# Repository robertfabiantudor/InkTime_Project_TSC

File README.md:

# InkTime Smartwatch

<br/>
<br/>

## Block Diagram

<br/>
<br/>

## Bill of Materials(BOM)

| Name | Component Type | Part Number | Qty | JLCPCB Part Link | Datasheet Link|
|----------|----------|------------|-----|----------------|-----------|
| ANT1 | Antenna | 2450AT18B100E | 1 | [View Part](https://jlcpcb.com/partdetail/JohansonDielectrics-2450AT18B100E/C2917717) | [View Datasheet](https://www.lcsc.com/datasheet/C2917717.pdf?spm=wm.sxq.inf.ggs___wm.ssy.bg.0.xh&lcsc_vid=RVILV1QAFgMLXlRXRFQPBVVeFgVaXwJQTwdfAlJXFAUxVlNRQVReVFZST1FWUDsOAxUeFF5JWBYZEEoKFBINSQcJGk4%3D) |
| C1, C2, C17, C18 | Capacitor | GRM0335C1H120JA01D | 4 | [View Part](https://jlcpcb.com/partdetail/MurataElectronics-GRM0335C1H120JA01D/C85890) | [View Datasheet](https://www.lcsc.com/datasheet/C85890.pdf?spm=wm.sxq.inf.ggs___wm.ssy.bg.0.xh&lcsc_vid=RVILV1QAFgMLXlRXRFQPBVVeFgVaXwJQTwdfAlJXFAUxVlNRQVReVFZQQFRdUzsOAxUeFF5JWBYZEEoKFBINSQcJGk4eFQsCAgIaSgADAwAHC0slRVhfUFNXQE8GEwkK) |
| C1-EP-DR, C24, C39 | Capacitor | GRM155R60J106ME44D | 3 | [View Part](https://jlcpcb.com/partdetail/MurataElectronics-GRM155R60J106ME44D/C76991) | [View Datasheet](https://www.lcsc.com/datasheet/C76991.pdf?spm=wm.sxq.inf.ggs___wm.ssy.bg.0.xh&lcsc_vid=RVILV1QAFgMLXlRXRFQPBVVeFgVaXwJQTwdfAlJXFAUxVlNRQVReVFdWQ1NfVTsOAxUeFF5JWBYZEEoKFBINSQcJGk4eFQsCAgIaSgADAwAHC0slT1RWXlRIHxUDCw%3D%3D) |
| C2-EP-DR | Capacitor | RVT1E4R7M0405 | 1 | [View Part](https://jlcpcb.com/partdetail/DMBJ-RVT1E4R7M0405_4_7UF25V/C970600) | [View Datasheet](https://www.lcsc.com/datasheet/C2895731.pdf?spm=wm.sxq.inf.ggs___wm.ssy.bg.0.xh&lcsc_vid=RVILV1QAFgMLXlRXRFQPBVVeFgVaXwJQTwdfAlJXFAUxVlNRQVReVFdRRVlcUjsOAxUeFF5JWBYZEEoKFBINSQcJGk4eFQsCAgIaSgADAwAHC0slRVlXUlNVRk8GEwkK) |
| C3, C4 | Capacitor | GRM0335C1H1R0BA01D | 2 | [View Part](https://jlcpcb.com/partdetail/MurataElectronics-GRM0335C1H1R0BA01D/C85893) | [View Datasheet](https://www.lcsc.com/datasheet/C85893.pdf?spm=wm.sxq.inf.ggs___wm.ssy.bg.0.xh&lcsc_vid=RVILV1QAFgMLXlRXRFQPBVVeFgVaXwJQTwdfAlJXFAUxVlNRQVReVFFVTlldVzsOAxUeFF5JWBYZEEoKFBINSQcJGk4dAgUUFAk%3D) |
| C5, C7, C8, C12, C19 | Capacitor | GRM033R60J104KE19D | 5 | [View Part](https://jlcpcb.com/partdetail/MurataElectronics-GRM033R60J104KE19D/C76928) | [View Datasheet](https://www.lcsc.com/datasheet/C76928.pdf?spm=wm.sxq.inf.ggs___wm.ssy.bg.0.xh&lcsc_vid=RVILV1QAFgMLXlRXRFQPBVVeFgVaXwJQTwdfAlJXFAUxVlNRQVReVFJTQlJcVDsOAxUeFF5JWBYZEEoKFBINSQcJGk4eFQsCAgIaSgADAwAHC0slRVlXUlNVRk8GEwkK) |
| C6, C14, C20, C21, C43 | Capacitor | GRM155R60J475KE96D | 5 | [View Part](https://jlcpcb.com/partdetail/MurataElectronics-GRM155R60J475KE96D/C76995) | [View Datasheet](https://www.lcsc.com/datasheet/C76995.pdf?spm=wm.sxq.inf.ggs___wm.ssy.bg.0.xh&lcsc_vid=RVILV1QAFgMLXlRXRFQPBVVeFgVaXwJQTwdfAlJXFAUxVlNRQVReVFNRR1VbVjsOAxUeFF5JWBYZEEoKFBINSQcJGk4dAgUUFAk%3D) |
| C9 | Capacitor | GRM033R71E821KA01D | 1 | [View Part](https://jlcpcb.com/partdetail/197002-GRM033R71E821KA01D/C185597) | [View Datasheet](https://www.lcsc.com/datasheet/C185597.pdf?spm=wm.sxq.inf.ggs___wm.ssy.bg.0.xh&lcsc_vid=RVILV1QAFgMLXlRXRFQPBVVeFgVaXwJQTwdfAlJXFAUxVlNRQVReVFxTQVVfVjsOAxUeFF5JWBYZEEoKFBINSQcJGk4dAgUUFAk%3D) |
| C11 | Capacitor | GRM0335C1E101JA01D | 1 | [View Part](https://jlcpcb.com/partdetail/MurataElectronics-GRM0335C1E101JA01D/C76917) | [View Datasheet](https://www.lcsc.com/datasheet/C76917.pdf?spm=wm.sxq.inf.ggs___wm.ssy.bg.0.xh&lcsc_vid=RVILV1QAFgMLXlRXRFQPBVVeFgVaXwJQTwdfAlJXFAUxVlNRQVReVF1QQ1JXVzsOAxUeFF5JWBYZEEoKFBINSQcJGk4eFQsCAgIaSgADAwAHC0slRlRfX1ZWT08GEwkK) |
| C15 | Capacitor | GRM155R60J105KE19D | 1 | [View Part](https://jlcpcb.com/partdetail/MurataElectronics-GRM155R60J105KE19D/C15684) | [View Datasheet](https://www.lcsc.com/product-detail/C15684.html?s_z=n_q_GRM155R60J105KE19D&spm=wm.ssy.bg.0.xh&lcsc_vid=RVILV1QAFgMLXlRXRFQPBVVeFgVaXwJQTwdfAlJXFAUxVlNRQVReU1ZQR1NbVTsOAxUeFF5JWBYZEEoKFBINSQcJGk4dAgUUFAk%3D) |
| C16, C10, C13, C22 | Capacitor | GRM033R60J473KE19D | 4 | [View Part](https://jlcpcb.com/parts/componentSearch?searchTxt=GRM033R60J473KE19D) | [View Datasheet](https://www.lcsc.com/product-detail/C85925.html?s_z=n_q_GRM033R60J473KE19D&spm=wm.ssy.bg.0.xh&lcsc_vid=RVILV1QAFgMLXlRXRFQPBVVeFgVaXwJQTwdfAlJXFAUxVlNRQVReU1RRTlFcUzsOAxUeFF5JWBYZEEoKFBINSQcJGk4dAgUUFAk%3D) |
| C25, C33 | Capacitor | GRM155R60J226ME11D | 2 | [View Part](https://jlcpcb.com/partdetail/408393-GRM155R60J226ME11D/C415703) | [View Datasheet](https://www.lcsc.com/datasheet/C415703.pdf?spm=wm.sxq.inf.ggs___wm.ssy.bg.0.xh&lcsc_vid=RVILV1QAFgMLXlRXRFQPBVVeFgVaXwJQTwdfAlJXFAUxVlNRQVReU1BSQlVdVjsOAxUeFF5JWBYZEEoKFBINSQcJGk4dAgUUFAk%3D) |
| C23, C27, C29, C30, C31, C32, C34, C37, C38, C42| Capacitor | GRM011R60J152KE01L | 10 | [View Part](https://jlcpcb.com/partdetail/22429554-GRM011R60J152KE01L/C21012218) | [View Datasheet](https://www.lcsc.com/datasheet/C21012218.pdf?spm=wm.sxq.inf.ggs___wm.ssy.bg.0.xh&lcsc_vid=RVILV1QAFgMLXlRXRFQPBVVeFgVaXwJQTwdfAlJXFAUxVlNRQVReU1FTRlhfUDsOAxUeFF5JWBYZEEoKFBINSQcJGk4eFQsCAgIaSgADAwAHC0slQFdXXlFIHxUDCw%3D%3D) |
| D2, D4, D5  | Schottky Diode | MBR0530 | 3 | [View Part](https://jlcpcb.com/partdetail/onsemi-MBR0530/C232832) | [View Datasheet](https://www.lcsc.com/datasheet/C232832.pdf?spm=wm.sxq.inf.ggs___wm.ssy.bg.3.xh&lcsc_vid=RVILV1QAFgMLXlRXRFQPBVVeFgVaXwJQTwdfAlJXFAUxVlNRQVReUlVUQlZXXjsOAxUeFF5JWBYZEEoKFBINSQcJGk4eFQsCAgIaSgADAwAHC0slQ1ZbUFVeWQkaCgg%3D) |
| D3 | ESD Protection | USBLC6-2SC6Y | 1 | [View Part](https://jlcpcb.com/partdetail/STMicroelectronics-USBLC62SC6Y/C2969755) | [View Datasheet](https://www.lcsc.com/datasheet/C2969755.pdf?spm=wm.sxq.inf.ggs___wm.ssy.bg.0.xh&lcsc_vid=RVILV1QAFgMLXlRXRFQPBVVeFgVaXwJQTwdfAlJXFAUxVlNRQVReUlZVQFReVjsOAxUeFF5JWBYZEEoKFBINSQcJGk4dAgUUFAk%3D) |
| EPD_C1, EPD_C2, EPD_C6–EPD_C12 | Capacitor | 0201WMJ0100TCE | 9 | [View Part](https://jlcpcb.com/partdetail/25795-0201WMJ0100TCE/C25052) | [View Datasheet](https://www.lcsc.com/datasheet/C25052.pdf?spm=wm.sxq.inf.ggs___wm.ssy.bg.0.xh&lcsc_vid=RVILV1QAFgMLXlRXRFQPBVVeFgVaXwJQTwdfAlJXFAUxVlNRQVReUVVSQFBcUjsOAxUeFF5JWBYZEEoKFBINSQcJGk4eFQsCAgIaSgADAwAHC0slRlNcU1dSWQkaCgg%3D) |
| EPD_C5 | Capacitor | 500R07W104KV4T | 1 | [View Part](https://jlcpcb.com/partdetail/6103901-500R07W104KV4T_0_1uF50v/C5337557) | [View Datasheet](https://www.mouser.com/catalog/specsheets/johanson_joha-s-a0008490164-1.pdf?_gl=1*1natqy3*_gcl_aw*R0NMLjE3NzY0NTE3MzMuQ2p3S0NBand0SWZQQmhBekVpd0F2OVJUSnBRX2lCajR0MlBzNHZ5MExvUnpFdC1mTmpicTQwR0hYM3ZmV1lEa1JYZ2ZDUGdWczVxMHBob0MyMXdRQXZEX0J3RQ..*_gcl_au*MTQ2MTI4OTM2Mi4xNzc2NDUxNjg3LjE4ODk2NzQyODAuMTc3NjUwMjIwNy4xNzc2NTAyNzAz*_ga*MTg0MjYwMjQxLjE3NzY0NTE2ODc.*_ga_15W4STQT4T*czE3NzY1MDYyOTckbzQkZzEkdDE3NzY1MDYzNjEkajYwJGwwJGgw) |
| IC1 | LiPo Charger | BQ25180YBGR | 1 | [View Part](https://jlcpcb.com/partdetail/TexasInstruments-BQ25180YBGR/C3682423) | [View Datasheet](https://www.ti.com/cn/lit/gpn/bq25180) |
| IC2 | Haptic Driver | DRV2605YZFR | 1 | [View Part](https://jlcpcb.com/partdetail/TexasInstruments-DRV2605YZFR/C81079) | [View Datasheet](https://www.lcsc.com/datasheet/C81079.pdf?spm=wm.sxq.inf.ggs___wm.ssy.bg.0.xh&lcsc_vid=RVILV1QAFgMLXlRXRFQPBVVeFgVaXwJQTwdfAlJXFAUxVlNRQVReUldeQ1RfVjsOAxUeFF5JWBYZEEoKFBINSQcJGk4eFQsCAgIaSgADAwAHC0slQ1BbUFRVWQkaCgg%3D) |
| IC3 | IMU | BMA421 | 1 | [View Part](https://jlcpcb.com/partdetail/BoschSensortec-BMA421/C5242966) | [View Datasheet](https://files.pine64.org/doc/datasheet/pinetime/BST-BMA421-FL000.pdf) |
| IC9 | DC/DC Converter | RT6160AWSC | 1 | [View Part](https://jlcpcb.com/partdetail/RichtekTech-RT6160AWSC/C7065276) | [View Datasheet](https://www.lcsc.com/datasheet/C7065276.pdf?spm=wm.sxq.inf.ggs___wm.ssy.bg.0.xh&lcsc_vid=RVILV1QAFgMLXlRXRFQPBVVeFgVaXwJQTwdfAlJXFAUxVlNRQVReUlFfQVZbUTsOAxUeFF5JWBYZEEoKFBINSQcJGk4dAgUUFAk%3D) |
| J1 | FPC Connector | 503480-2400 | 1 | [View Part](https://jlcpcb.com/partdetail/MOLEX-5034802400/C122434) | [View Datasheet](https://www.lcsc.com/datasheet/C122434.pdf?spm=wm.sxq.inf.ggs___wm.ssy.bg.0.xh&lcsc_vid=RVILV1QAFgMLXlRXRFQPBVVeFgVaXwJQTwdfAlJXFAUxVlNRQVReUlJeQ1JeVzsOAxUeFF5JWBYZEEoKFBINSQcJGk4dAgUUFAk%3D) |
| J2 | Debug Connector | TC2030-IDC | 1 | - | [View Datasheet](https://www.tag-connect.com/wp-content/uploads/bsk-pdf-manager/2019/12/TC2030-IDC-Datasheet-Rev-B.pdf) |
| J4 | USB-C Connector | KH-TYPE-C-16P | 1 | [View Part](https://jlcpcb.com/partdetail/Shenzhen_KinghelmElec-KH_TYPE_C16P/C709357) | [View Datasheet](https://www.lcsc.com/datasheet/C709357.pdf?spm=wm.sxq.inf.ggs___wm.ssy.bg.0.xh&lcsc_vid=RVILV1QAFgMLXlRXRFQPBVVeFgVaXwJQTwdfAlJXFAUxVlNRQVReUlNQQldXVDsOAxUeFF5JWBYZEEoKFBINSQcJGk4eFQsCAgIaSgADAwAHC0slRFdWVVBURE8GEwkK) |
| L1 | Inductor | LQG15HS3N9S02D | 1 | [View Part](https://jlcpcb.com/partdetail/MurataElectronics-LQG15HS3N9S02D/C77109) | [View Datasheet](https://www.lcsc.com/datasheet/C77109.pdf?spm=wm.sxq.inf.ggs___wm.ssy.bg.0.xh&lcsc_vid=RVILV1QAFgMLXlRXRFQPBVVeFgVaXwJQTwdfAlJXFAUxVlNRQVReUVBfQVJdVjsOAxUeFF5JWBYZEEoKFBINSQcJGk4dAgUUFAk%3D) |
| L2 | Inductor | LQW15DN100M00D | 1 | [View Part](https://jlcpcb.com/partdetail/MurataElectronics-LQW15DN100M00D/C910650) | [View Datasheet](https://www.lcsc.com/datasheet/C910650.pdf?spm=wm.sxq.inf.ggs___wm.ssy.bg.0.xh&lcsc_vid=RVILV1QAFgMLXlRXRFQPBVVeFgVaXwJQTwdfAlJXFAUxVlNRQVReUVJXR1BdVjsOAxUeFF5JWBYZEEoKFBINSQcJGk4eFQsCAgIaSgADAwAHC0slRVReUlZIHxUDCw%3D%3D) |
| L3 | Inductor | LQG15HS15NJ02D| 1 | [View Part](https://jlcpcb.com/partdetail/MurataElectronics-LQG15HS15NJ02D/C86059) | [View Datasheet](https://www.lcsc.com/datasheet/C86059.pdf?spm=wm.sxq.inf.ggs___wm.ssy.bg.0.xh&lcsc_vid=RVILV1QAFgMLXlRXRFQPBVVeFgVaXwJQTwdfAlJXFAUxVlNRQVReUVJfRlJaVzsOAxUeFF5JWBYZEEoKFBINSQcJGk4dAgUUFAk%3D) |
| L5 | Inductor | LQG15HS27NJ02D | 1 | [View Part](https://jlcpcb.com/partdetail/MurataElectronics-LQG15HS27NJ02D/C12669) | [View Datasheet](https://www.lcsc.com/datasheet/C12669.pdf?spm=wm.sxq.inf.ggs___wm.ssy.bg.0.xh&lcsc_vid=RVILV1QAFgMLXlRXRFQPBVVeFgVaXwJQTwdfAlJXFAUxVlNRQVReUVNVR1hcXzsOAxUeFF5JWBYZEEoKFBINSQcJGk4dAgUUFAk%3D) |
| L7 | Inductor | LQW15CNR47K10D| 1 | [View Part](https://jlcpcb.com/partdetail/MurataElectronics-LQW15CNR47K10D/C913544) | [View Datasheet](https://www.lcsc.com/datasheet/C913544.pdf?spm=wm.sxq.inf.ggs___wm.ssy.bg.0.xh&lcsc_vid=RVILV1QAFgMLXlRXRFQPBVVeFgVaXwJQTwdfAlJXFAUxVlNRQVReUVNRT1dbVjsOAxUeFF5JWBYZEEoKFBINSQcJGk4eFQsCAgIaSgADAwAHC0slQFZfV11IHxUDCw%3D%3D) |
| Q1 | P-Channel MOSFET | DMG2305UX-7 | 1 | [View Part](https://jlcpcb.com/partdetail/DiodesIncorporated-DMG2305UX7/C150470) | [View Datasheet](https://www.lcsc.com/datasheet/C150470.pdf?spm=wm.sxq.inf.ggs___wm.ssy.bg.0.xh&lcsc_vid=RVILV1QAFgMLXlRXRFQPBVVeFgVaXwJQTwdfAlJXFAUxVlNRQVReUVxRQFhXUzsOAxUeFF5JWBYZEEoKFBINSQcJGk4dAgUUFAk%3D) |
| Q3 | N-Channel MOSFET | SI1308EDL-T1-GE3 | 1 | [View Part](https://jlcpcb.com/partdetail/VishayIntertech-SI1308EDL_T1GE3/C469327) | [View Datasheet](https://www.lcsc.com/datasheet/C469327.pdf?spm=wm.sxq.inf.ggs___wm.ssy.bg.0.xh&lcsc_vid=RVILV1QAFgMLXlRXRFQPBVVeFgVaXwJQTwdfAlJXFAUxVlNRQVReUVBWQ1VdVDsOAxUeFF5JWBYZEEoKFBINSQcJGk4eFQsCAgIaSgADAwAHC0slQFFYUlZRQU8GEwkK) |
| R_PWR_EPD, R2_EP_DR, R9 | Resistor | CPF0201D10KC1 | 3 | [View Part](https://jlcpcb.com/partdetail/TEConnectivity-CPF0201D10KC1/C4187156) | [View Datasheet](https://www.lcsc.com/datasheet/C4187156.pdf?spm=wm.sxq.inf.ggs___wm.ssy.bg.0.xh&lcsc_vid=RVILV1QAFgMLXlRXRFQPBVVeFgVaXwJQTwdfAlJXFAUxVlNRQVReUFdQR1hYVjsOAxUeFF5JWBYZEEoKFBINSQcJGk4eFQsCAgIaSgADAwAHC0slRlReU1NWWQkaCgg%3D) |
| R_TYPE_SEL | Resistor | RC0201FR-072R2L | 1 | [View Part](https://jlcpcb.com/partdetail/YAGEO-RC0201FR072R2L/C138154) | [View Datasheet](https://www.lcsc.com/datasheet/C138154.pdf?spm=wm.sxq.inf.ggs___wm.ssy.bg.0.xh&lcsc_vid=RVILV1QAFgMLXlRXRFQPBVVeFgVaXwJQTwdfAlJXFAUxVlNRQVReUFBTQlhcVDsOAxUeFF5JWBYZEEoKFBINSQcJGk4dAgUUFAk%3D) |
| R1_EP_DR | Resistor | 25121WF470LT4E | 1 | [View Part](https://jlcpcb.com/partdetail/21809-25121WF470LT4E/C21097) | [View Datasheet](https://www.lcsc.com/datasheet/C21097.pdf?spm=wm.sxq.inf.ggs___wm.ssy.bg.0.xh&lcsc_vid=RVILV1QAFgMLXlRXRFQPBVVeFgVaXwJQTwdfAlJXFAUxVlNRQVReUFJWT1lbVTsOAxUeFF5JWBYZEEoKFBINSQcJGk4dAgUUFAk%3D) |
| R1_USB1, R2_USB | Resistor | RC0201JR-075K1L | 2 | [View Part](https://jlcpcb.com/partdetail/YAGEO-RC0201JR075K1L/C163490) | [View Datasheet](https://www.lcsc.com/datasheet/C163490.pdf?spm=wm.sxq.inf.ggs___wm.ssy.bg.0.xh&lcsc_vid=RVILV1QAFgMLXlRXRFQPBVVeFgVaXwJQTwdfAlJXFAUxVlNRQVReUFJRT1NbUjsOAxUeFF5JWBYZEEoKFBINSQcJGk4dAgUUFAk%3D) |
| R2, R3, R4 | Resistor | RC0201FR-070RL | 3 | [View Part](https://jlcpcb.com/partdetail/YAGEO-RC0201FR070RL/C106227) | [View Datasheet](https://www.lcsc.com/datasheet/C106227.pdf?spm=wm.sxq.inf.ggs___wm.ssy.bg.0.xh&lcsc_vid=RVILV1QAFgMLXlRXRFQPBVVeFgVaXwJQTwdfAlJXFAUxVlNRQVReUFNVQ1NcUTsOAxUeFF5JWBYZEEoKFBINSQcJGk4dAgUUFAk%3D) |
| R5, R7, R8 | Resistor | RC0201FR-0710KL | 3 | [View Part](https://jlcpcb.com/partdetail/YAGEO-RC0201FR0710KL/C106225) | [View Datasheet](https://www.lcsc.com/product-detail/C106225.html?s_z=n_q_RC0201FR-0710KL&spm=wm.ssy.bg.0.xh&lcsc_vid=RVILV1QAFgMLXlRXRFQPBVVeFgVaXwJQTwdfAlJXFAUxVlNRQVReUFxUQFVaUjsOAxUeFF5JWBYZEEoKFBINSQcJGk4eFQsCAgIaSgADAwAHC0slRlJWVlFSWQkaCgg%3D) |
| R17, R18 | Resistor | AC0201FR-073K3L | 2 | [View Part](https://jlcpcb.com/partdetail/YAGEO-AC0201FR073K3L/C226534) | [View Datasheet](https://www.lcsc.com/datasheet/C226534.pdf?spm=wm.sxq.inf.ggs___wm.ssy.bg.0.xh&lcsc_vid=RVILV1QAFgMLXlRXRFQPBVVeFgVaXwJQTwdfAlJXFAUxVlNRQVReUFxRR1hYUTsOAxUeFF5JWBYZEEoKFBINSQcJGk4eFQsCAgIaSgADAwAHC0slRlFYVVZRWQkaCgg%3D) |
| SW_DN, SW_ENT, SW_UP | Button | EVP-AKE31A | 3 | [View Part](https://jlcpcb.com/partdetail/PANASONIC-EVPAKE31A/C569760) | [View Datasheet](https://www.lcsc.com/datasheet/C569760.pdf?spm=wm.sxq.inf.ggs___wm.ssy.bg.0.xh&lcsc_vid=RVILV1QAFgMLXlRXRFQPBVVeFgVaXwJQTwdfAlJXFAUxVlNRQVReUV1VQ1VYVTsOAxUeFF5JWBYZEEoKFBINSQcJGk4eFQsCAgIaSgADAwAHC0slTlBdUlBSWQkaCgg%3D) |
| U1 | MCU | NRF52840-QIAA-R | 1 | [View Part](https://jlcpcb.com/partdetail/NordicSemicon-NRF52840_QIAAR/C190794) | [View Datasheet](https://www.lcsc.com/datasheet/C190794.pdf?spm=wm.sxq.inf.ggs___wm.ssy.bg.0.xh&lcsc_vid=RVILV1QAFgMLXlRXRFQPBVVeFgVaXwJQTwdfAlJXFAUxVlNRQVReUF1RQlJbXzsOAxUeFF5JWBYZEEoKFBINSQcJGk4eFQsCAgIaSgADAwAHC0slRVdWVVJXQU8GEwkK) |
| U3 | Fuel Gauge | MAX17048G+T10 | 1 | [View Part](https://jlcpcb.com/partdetail/2777647-MAX17048GT10/C2682616) | [View Datasheet](https://www.lcsc.com/datasheet/C2682616.pdf?spm=wm.sxq.inf.ggs___wm.ssy.bg.0.xh&lcsc_vid=RVILV1QAFgMLXlRXRFQPBVVeFgVaXwJQTwdfAlJXFAUxVlNRQVReUF1WQVJaXzsOAxUeFF5JWBYZEEoKFBINSQcJGk4eFQsCAgIaSgADAwAHC0slRVBeXlNIHxUDCw%3D%3D) |
| X1 | Crystal | X201232768KJD2SI | 1 | [View Part](https://jlcpcb.com/partdetail/357115-X201232768KJD2SI/C383843) | [View Datasheet](https://www.lcsc.com/datasheet/C383843.pdf?spm=wm.sxq.inf.ggs___wm.ssy.bg.0.xh&lcsc_vid=RVILV1QAFgMLXlRXRFQPBVVeFgVaXwJQTwdfAlJXFAUxVlNRQVReX1FSQlVdUDsOAxUeFF5JWBYZEEoKFBINSQcJGk4eFQsCAgIaSgADAwAHC0slQ1BWUFVTQU8GEwkK) |
| X2 | Crystal | X322532MOB4SI | 1 | [View Part](https://jlcpcb.com/partdetail/YXC_CrystalOscillators-X322532MOB4SI/C9009) | [View Datasheet](https://www.lcsc.com/datasheet/C9009.pdf?spm=wm.sxq.inf.ggs___wm.ssy.bg.0.xh&lcsc_vid=RVILV1QAFgMLXlRXRFQPBVVeFgVaXwJQTwdfAlJXFAUxVlNRQVReX1BTRFhZXjsOAxUeFF5JWBYZEEoKFBINSQcJGk4eFQsCAgIaSgADAwAHC0slRlheUF1SWQkaCgg%3D) |

<br/>
<br/>

## Hardware Functionality
### Overview
The system is built around the **nRF52840 microcontroller**, which controls all peripherals and manages communication between them. The design is centered on low power consumption and efficient interaction between modules.

<br/>

### Power Management
- Power is supplied through the **USB-C connector**, protected by an **ESD protection circuit**.  
- The input voltage is managed by the **LiPo charger**, which charges the battery and provides power to the system.
- A **DC/DC converter** generates a stable voltage of **3.3V** used by all components, ensuring consistent operation regardless of battery level.
- The **Fuel Gauge** monitors battery status and provides charge information to the MCU.

<br/>

### Communication Interfaces
- **I2C Bus**
  - Used by: IMU, Fuel Gauge, Haptic Driver, LiPo Charger  
  - Provides communication over shared **SDA** and **SCL** lines  
  - Allows multiple low-speed peripherals to be connected on the same bus  
  - Operates at standard or fast mode speeds, sufficient for sensor data and status monitoring  

- **SPI Bus**
  - Used by: E-Paper Display  
  - Enables fast data transfer required for updating the display  
  - Uses dedicated lines for clock and data, allowing higher throughput compared to I2C  

- **USB**
  - Used for power input and battery charging  
  - Can also be used for firmware upload or data communication if needed  

- **SWD**
  - Used for programming and debugging  
  - Provides direct access to the microcontroller for firmware flashing and real-time debugging

<br/>

### Display
- The **E-Paper display** is connected via an FPC connector and controlled through the SPI interface.  
- A dedicated **E-Paper driver circuit** manages the display operation.
- E-paper technology only consumes power while refreshing the image, which makes it well suited for low-power applications. To take full advantage of this, the display is powered through a controlled power switch, allowing it to be completely turned off when not actively used. This approach significantly reduces overall power consumption and extends battery life, especially in scenarios where the display content does not need to be updated frequently.

<br/>

### Sensors and Feedback Systems
- **IMU**  
  - The IMU is an accelerometer that is used for motion detection and activity tracking. 
  - It detects movement, orientation, steps and it can generate interrupts so the microcontroller only wakes up when needed, improving power efficiency.

- **Haptic Driver & Shaker**  
  - The haptic driver controls a vibration motor that provides user feedback. 
  - It is configured through I2C and can trigger predefined vibration patterns for notifications.

<br/>

### User Inputs
- **Buttons**  
  - The buttons are connected to GPIO pins and are used to detect user actions. 
  - They can trigger interrupts, allowing the system to wake from low-power states and respond quickly.

<br/>

### Wireless Connectivity
- **Antenna**  
  - The antenna is connected to the microcontroller's RF pin and is used for Low Energy communication via Bluetooth.
  - It enables wireless data exchange with external devices such as smartphones.

<br/>

### Debug Interface
- **Serial Wire Debug (SWD)**  
  - The SWD interface is used for programming and debugging the system during development. 
  - It provides direct access to the microcontroller for firmware upload and troubleshooting.

<br/>
<br/>

## MCU Pin Assignment
| Pin Names            | Purpose                                                                 | Target Component              |
|----------------------|-------------------------------------------------------------------------|-------------------------------|
| DEC1-DEC6, DEC3V3    | Decoupling pins for stable internal power                               | External Decoupling Capacitors|
| P0.00/XL1, P0.01/XL2 | Used to connect external 32.768 kHz Crystal Oscillator (X2)             | X2 Crystal Oscillator         |
| P0.26                | Unused                                                                  | Not connected                 |
| P0.27                | Unused                                                                  | Not connected                 |
| P0.04/AIN2           | Unused                                                                  | Not connected                 |
| P0.05/AIN3           | Chip Select (CS) - Enables communication with the display controller    | E-Paper Display               |
| P0.06, P0.07         | SDA & SCL - Used as shared I2C communication lines for connected devices| IMU, Fuel Gauge, Haptic Driver, LiPo Charger |
| P0.08, P1.08         | Used to receive interrupt signals from the accelerometer                | IMU                           |
| P1.09                | Unused                                                                  | Not connected                 |
| P0.11                | PMIC Interrupt - Indicates charging or power events                     | LiPo Charger                  |
| P0.12                | Haptic Enable: Sends a signal to activate the vibration motor           | Haptic Driver                 |
| VDD, VDDH            | Supply power to the system                                              | DC/DC Converter               |
| DCCH                 | Unused                                                                  | Not connected                 |
| VBUS                 | Detects when USB power is present                                       | USB-C Connector               |
| D-, D+               | Carry USB data signals for communication                                | USB-C Connector               |
| P0.13, P0.14, P1.02  | Connected to physical buttons for user input                            | Buttons                       |
| P0.15, P0.16, P0.17  | Used to control the display by selecting data or commands, resetting it when needed and checking if it is busy during updates | E-Paper Display |
| P0.18/RESET          | Hardware reset signal                                                   | Reset Circuit                 |
| P0.19                | Unused                                                                  | Not connected                 |
| P0.20                | Unused                                                                  | Not connected                 |
| P0.21                | Unused                                                                  | Not connected                 |
| P0.22                | Unused                                                                  | Not connected                 |
| P0.23                | Unused                                                                  | Not connected                 |
| P0.24                | Unused                                                                  | Not connected                 |
| P0.25                | Unused                                                                  | Not connected                 |
| P1.00                | Used for Serial Wire Output to send debug and trace data during development | Debug Interface (SWO)   |
| VSS, VSS_PAD, VSS_PA | Ground connections                                                     | Main Ground Plane             |
| XC1, XC2             | Provide the main high-frequency clock for the system and radio         | X1 Crystal Oscillator         |
| ANT                  | Connects the RF signal to the antenna                                   | Antenna                       |
| P0.10/NFC2           | Fuel Gauge Alert - Signals low battery                                  | Fuel Gauge                    |
| P0.09/NFC1           | Unused                                                                  | Not connected                 |
| P1.07                | Unused                                                                  | Not connected                 |
| P1.06                | Unused                                                                  | Not connected                 |
| P1.05                | Unused                                                                  | Not connected                 |
| P1.04                | Unused                                                                  | Not connected                 |
| P1.03                | Unused                                                                  | Not connected                 |
| P1.01                | Controls the power to the e-paper display by turning it on or off to save battery | E-Paper Power Switch (Q1 MOSFET) |
| SWDIO, SWDCLK        | Used for programming and debugging through the SWD interface           | Debug Port                    |
| DCC                  | Output from internal voltage regulators                                | LC Filter Circuit                        |
| P0.31/AIN7           | Unused                                                                  | Not connected                 |
| P0.30/AIN6           | Unused                                                                  | Not connected                 |
| P0.29/AIN5           | Unused                                                                  | Not connected                 |
| P0.28/AIN4           | Unused                                                                  | Not connected                 |
| P0.02/AIN0           | SPI Clock (SCK) - Synchronizes data sent to the display                | E-Paper Display               |
| P0.03/AIN1           | SPI Data Line (MOSI) -      Sends data to the display                  | E-Paper Display               |
| P1.15                | Unused                                                                  | Not connected                 |
| P1.14                | Unused                                                                  | Not connected                 |
| P1.13                | Unused                                                                  | Not connected                 |
| P1.12                | Unused                                                                  | Not connected                 |
| P1.11                | Unused                                                                  | Not connected                 |
| P1.10                | Unused                                                                  | Not connected                 |

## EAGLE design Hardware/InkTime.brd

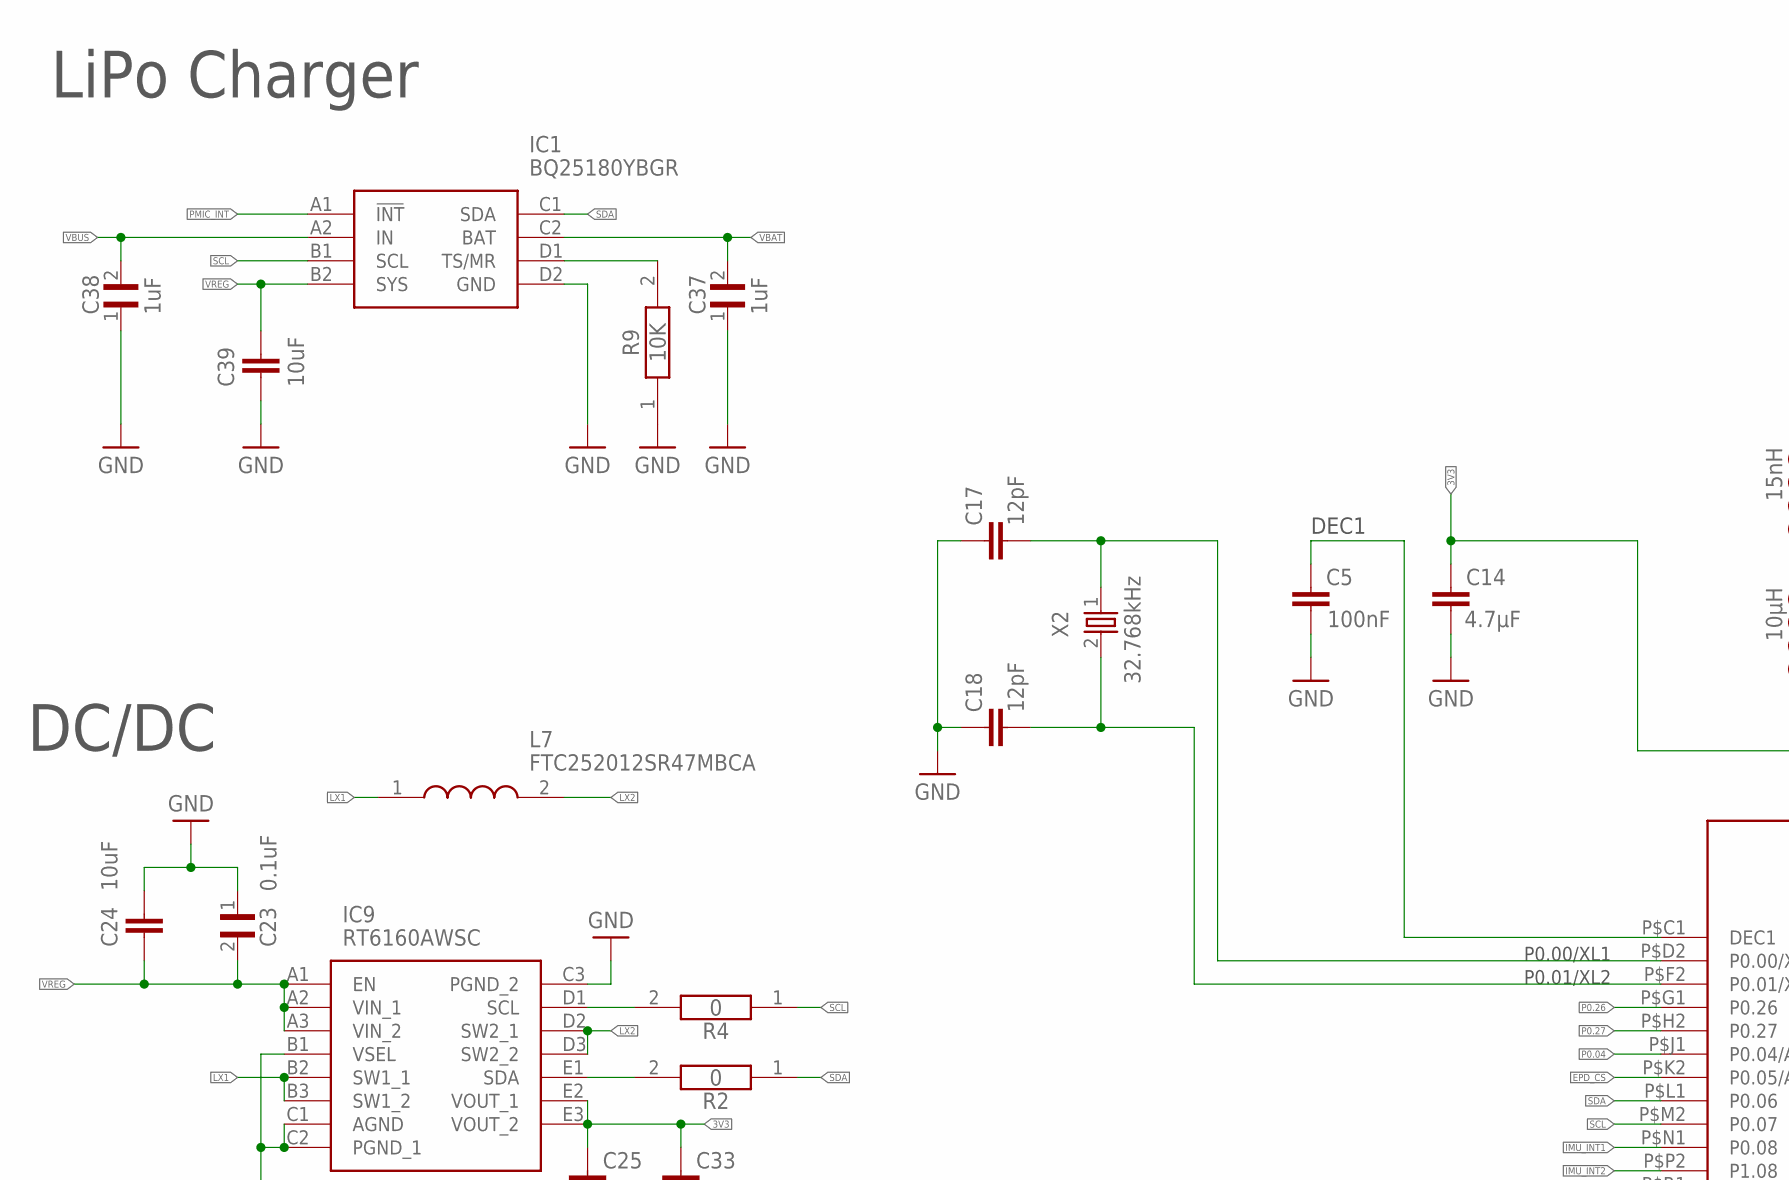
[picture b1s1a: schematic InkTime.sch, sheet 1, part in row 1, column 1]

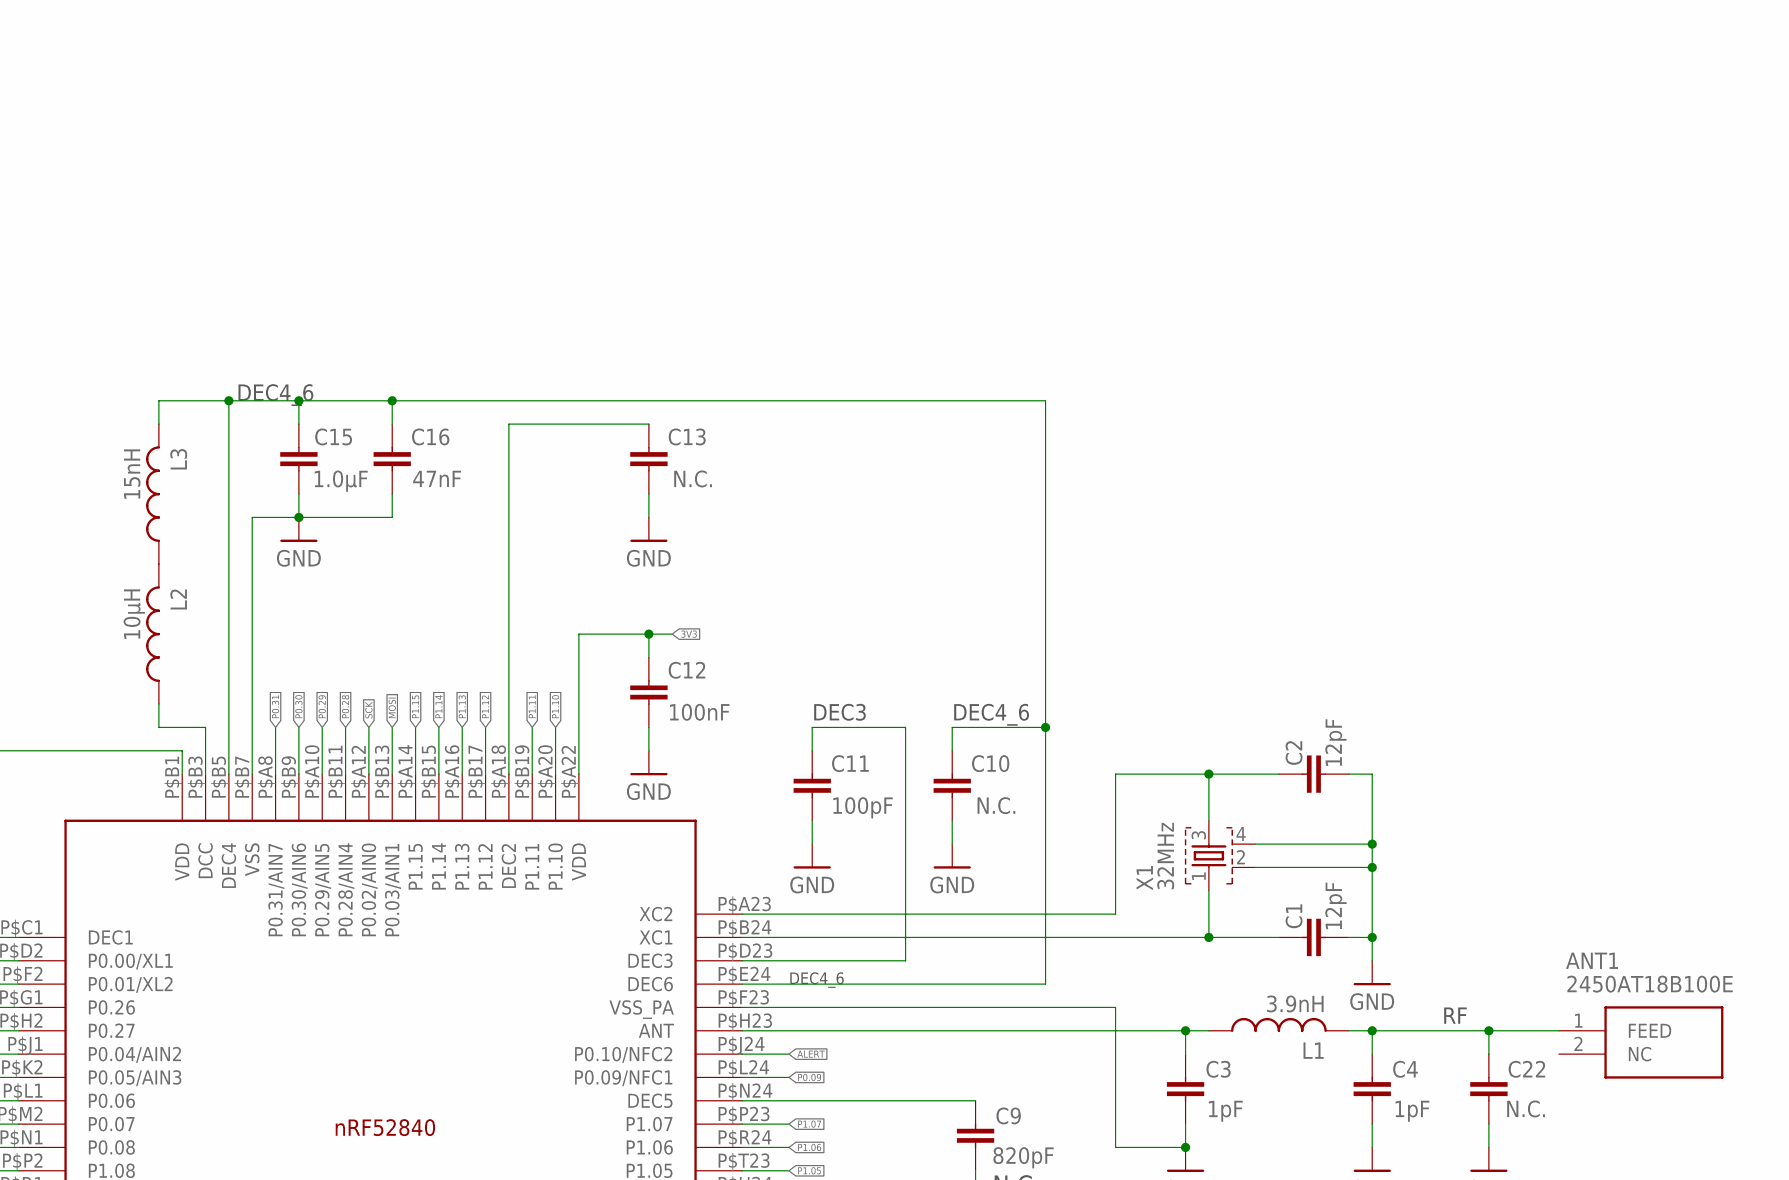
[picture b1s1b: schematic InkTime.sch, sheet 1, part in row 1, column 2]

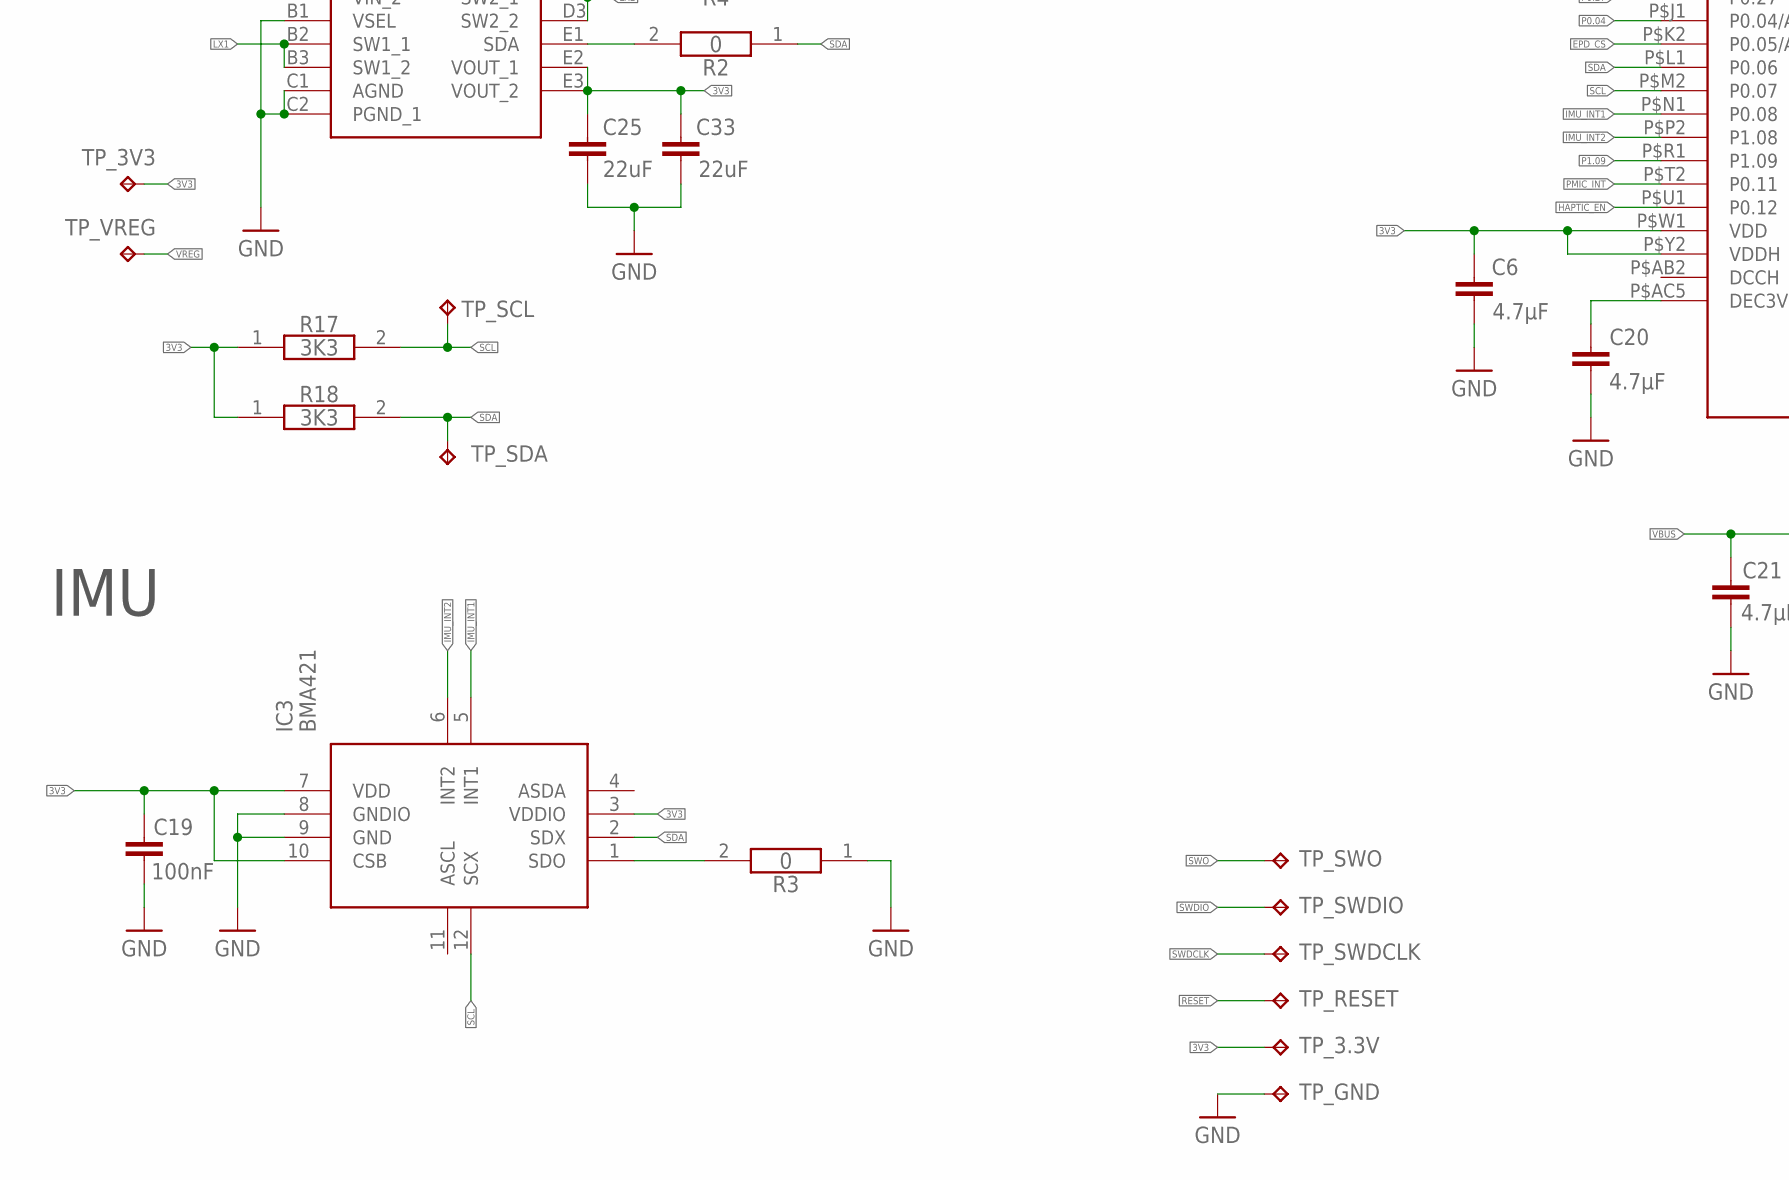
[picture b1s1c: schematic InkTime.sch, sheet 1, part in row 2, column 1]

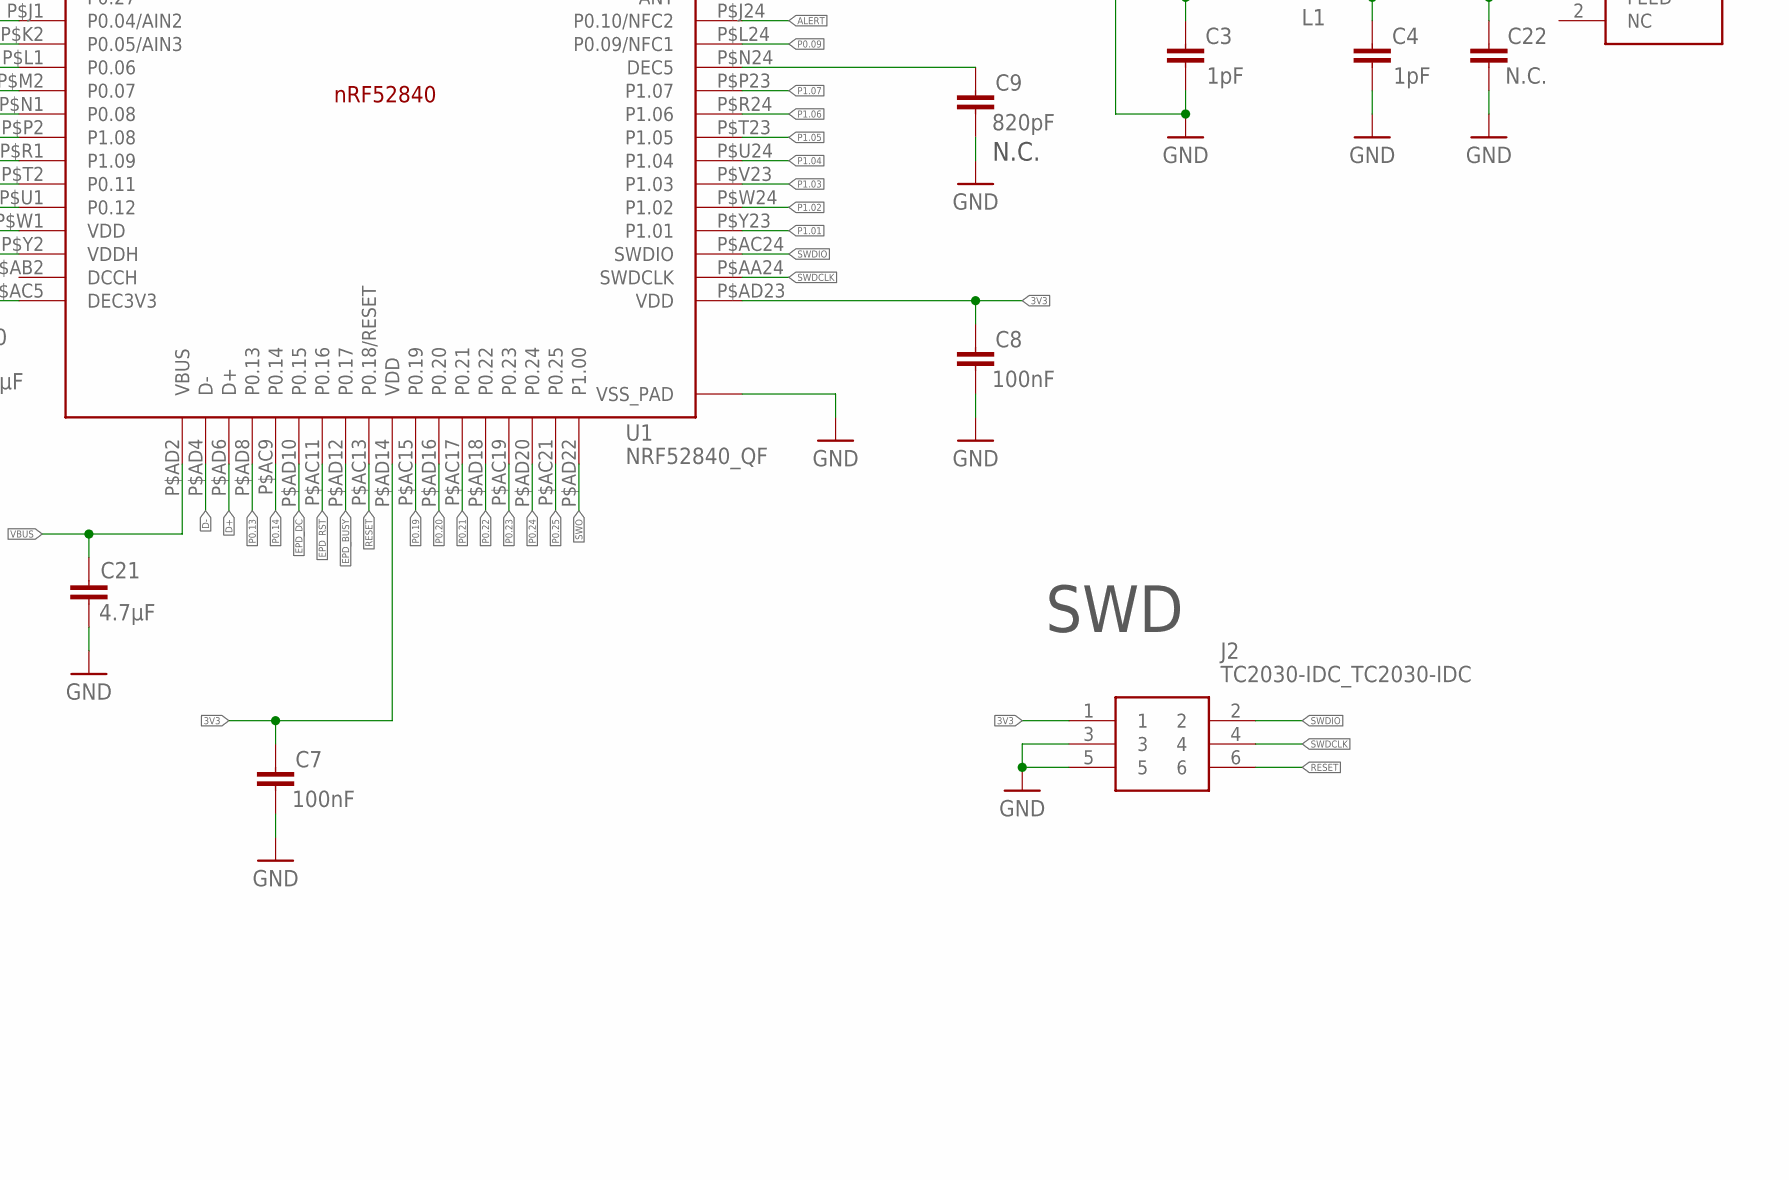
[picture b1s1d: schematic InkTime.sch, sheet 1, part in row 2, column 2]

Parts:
ANT1: 2450AT18B100E; 2450AT18B100E_ANTC3216X140N
C1, C2, C17, C18: 12pF; NORDIC_NRF_3_RESC0201_L
C3, C4: 1pF; NORDIC_NRF_3_RESC0201_L
C5, C7, C8, C12, C19: 100nF; NORDIC_NRF_3_RESC0201_L
C6, C14, C20, C21: 4.7µF; NORDIC_NRF_3_RESC0402_L
C9: 820pF; NORDIC_NRF_3_RESC0201_L
C10, C13, C22: N.C.; NORDIC_NRF_3_RESC0201_L
C11: 100pF; NORDIC_NRF_3_RESC0201_L
C15: 1.0µF; NORDIC_NRF_3_RESC0402_L
C16: 47nF; NORDIC_NRF_3_RESC0201_L
C23: 0.1uF; GRM011R60J152KE01L_1_0201
C24, C39: 10uF; NORDIC_NRF_3_RESC0402_L
C25, C33: 22uF; NORDIC_NRF_3_RESC0402_L
C37, C38: 1uF; GRM011R60J152KE01L_1_0201
IC1: BQ25180YBGR; BQ25180YBGR_BGA8C40P2X4_100X155X50
IC3: BMA421; BMA423_BMA423
IC9: RT6160AWSC; RT6160AWSC_BGA15C40P3X5_140X230X60
J2: TC2030-IDC_TC2030-IDC; TC2030-IDC_TC2030IDC
L1: 3.9nH; NORDIC_NRF_2_RESC0402_L
L2: 10µH; NORDIC_NRF_2_RESC0402_L
L3: 15nH; NORDIC_NRF_2_RESC0402_L
L7: FTC252012SR47MBCA; MLP2016SR47MT0S1_INDC2016X100N
R2, R3, R4: 0; CPF0201D7K68C1_0201
R9: 10K; CPF0201D7K68C1_0201
R17, R18: 3K3; CPF0201D7K68C1_0201
TP_3.3V, TP_3V3: HECTOR_WATCH_1_TPTP20R; HECTOR_WATCH_1_TP20R
TP_GND: HECTOR_WATCH_1_TPTP20R; HECTOR_WATCH_1_TP20R
TP_RESET: HECTOR_WATCH_1_TPTP20R; HECTOR_WATCH_1_TP20R
TP_SCL: HECTOR_WATCH_1_TPTP20R; HECTOR_WATCH_1_TP20R
TP_SDA: HECTOR_WATCH_1_TPTP20R; HECTOR_WATCH_1_TP20R
TP_SWDCLK: HECTOR_WATCH_1_TPTP20R; HECTOR_WATCH_1_TP20R
TP_SWDIO: HECTOR_WATCH_1_TPTP20R; HECTOR_WATCH_1_TP20R
TP_SWO: HECTOR_WATCH_1_TPTP20R; HECTOR_WATCH_1_TP20R
TP_VREG: HECTOR_WATCH_1_TPTP20R; HECTOR_WATCH_1_TP20R
U1: NRF52840_QF; NORDIC_NRF_4_AQFN50P700X700X85_HS-74N
X1: 32MHz; NORDIC_NRF_BT-XTAL_2016_N
X2: 32.768kHz; NORDIC_NRF_1_XTAL_3215_N

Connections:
3V3: C6.1, C7.1, C8.1, C12.1, C14.1, C19.1, C25.1, C33.1, IC3.3 (VDDIO), IC3.7 (VDD), IC3.10 (CSB), IC9.E2 (VOUT_1), IC9.E3 (VOUT_2), J2.1, R17.1, R18.1, TP_3.3V.TP, TP_3V3.TP, U1.P$A22 (VDD), U1.P$AD14 (VDD), U1.P$AD23 (VDD), U1.P$B1 (VDD), U1.P$W1 (VDD), U1.P$Y2 (VDDH); also elsewhere on the board
ALERT: U1.P$J24 (P0.10/NFC2); also elsewhere on the board
D+: U1.P$AD6 (D+); also elsewhere on the board
D-: U1.P$AD4 (D-); also elsewhere on the board
EPD_BUSY: U1.P$AD12 (P0.17); also elsewhere on the board
EPD_CS: U1.P$K2 (P0.05/AIN3); also elsewhere on the board
EPD_DC: U1.P$AD10 (P0.15); also elsewhere on the board
EPD_RST: U1.P$AC11 (P0.16); also elsewhere on the board
GND: C1.2, C2.2, C3.2, C4.2, C5.2, C6.2, C7.2, C8.2, C9.2, C10.2, C11.2, C12.2, C13.2, C14.2, C15.2, C16.2, C17.1, C18.1, C19.2, C20.2, C21.2, C22.2, C23.1, C24.1, C25.2, C33.2, C37.1, C38.1, C39.2, IC1.D2 (GND), IC3.8 (GNDIO), IC3.9 (GND), IC9.B1 (VSEL), IC9.C1 (AGND), IC9.C2 (PGND_1), IC9.C3 (PGND_2), J2.3, J2.5, R3.1, R9.1, TP_GND.TP, U1.P$74 (VSS_PAD), U1.P$75 (VSS_PAD), U1.P$76 (VSS_PAD), U1.P$77 (VSS_PAD), U1.P$78 (VSS_PAD), U1.P$79 (VSS_PAD), U1.P$80 (VSS_PAD), U1.P$81 (VSS_PAD), U1.P$82 (VSS_PAD), U1.P$83 (VSS_PAD), U1.P$84 (VSS_PAD), U1.P$85 (VSS_PAD), U1.P$86 (VSS_PAD), U1.P$87 (VSS_PAD), U1.P$88 (VSS_PAD), U1.P$89 (VSS_PAD), U1.P$90 (VSS_PAD), U1.P$B7 (VSS), U1.P$F23 (VSS_PA), X1.2, X1.4; also elsewhere on the board
HAPTIC_EN: U1.P$U1 (P0.12); also elsewhere on the board
IMU_INT1: IC3.5 (INT1), U1.P$N1 (P0.08)
IMU_INT2: IC3.6 (INT2), U1.P$P2 (P1.08)
LX1: IC9.B2 (SW1_1), IC9.B3 (SW1_2), L7.1
LX2: IC9.D2 (SW2_1), IC9.D3 (SW2_2), L7.2
MOSI: U1.P$B13 (P0.03/AIN1); also elsewhere on the board
unnamed: C9.1, U1.P$N24 (DEC5)
unnamed: C3.1, L1.1, U1.P$H23 (ANT)
unnamed: C13.1, U1.P$A18 (DEC2)
unnamed: L2.1, U1.P$B3 (DCC)
unnamed: IC1.D1 (TS/MR), R9.2
unnamed: C11.1, U1.P$D23 (DEC3)
unnamed: C1.1, U1.P$B24 (XC1), X1.1
unnamed: C2.1, U1.P$A23 (XC2), X1.3
unnamed: ANT1.1 (FEED), C4.1, C22.1, L1.2
unnamed: C10.1, C15.1, C16.1, L3.2, U1.P$B5 (DEC4), U1.P$E24 (DEC6)
unnamed: L2.2, L3.1
unnamed: C5.1, U1.P$C1 (DEC1)
unnamed: C17.2, U1.P$D2 (P0.00/XL1), X2.1
unnamed: C18.2, U1.P$F2 (P0.01/XL2), X2.2
unnamed: C20.1, U1.P$AC5 (DEC3V3)
unnamed: IC9.E1 (SDA), R2.2
unnamed: IC9.D1 (SCL), R4.2
unnamed: IC3.1 (SDO), R3.2
P0.04: U1.P$J1 (P0.04/AIN2)
P0.09: U1.P$L24 (P0.09/NFC1)
P0.13: U1.P$AD8 (P0.13); also elsewhere on the board
P0.14: U1.P$AC9 (P0.14); also elsewhere on the board
P0.19: U1.P$AC15 (P0.19)
P0.20: U1.P$AD16 (P0.20)
P0.21: U1.P$AC17 (P0.21)
P0.22: U1.P$AD18 (P0.22)
P0.23: U1.P$AC19 (P0.23)
P0.24: U1.P$AD20 (P0.24)
P0.25: U1.P$AC21 (P0.25)
P0.26: U1.P$G1 (P0.26)
P0.27: U1.P$H2 (P0.27)
P0.28: U1.P$B11 (P0.28/AIN4)
P0.29: U1.P$A10 (P0.29/AIN5)
P0.30: U1.P$B9 (P0.30/AIN6)
P0.31: U1.P$A8 (P0.31/AIN7)
P1.01: U1.P$Y23 (P1.01); also elsewhere on the board
P1.02: U1.P$W24 (P1.02); also elsewhere on the board
P1.03: U1.P$V23 (P1.03)
P1.04: U1.P$U24 (P1.04)
P1.05: U1.P$T23 (P1.05)
P1.06: U1.P$R24 (P1.06)
P1.07: U1.P$P23 (P1.07)
P1.09: U1.P$R1 (P1.09)
P1.10: U1.P$A20 (P1.10)
P1.11: U1.P$B19 (P1.11)
P1.12: U1.P$B17 (P1.12)
P1.13: U1.P$A16 (P1.13)
P1.14: U1.P$B15 (P1.14)
P1.15: U1.P$A14 (P1.15)
PMIC_INT: IC1.A1 (!INT), U1.P$T2 (P0.11)
RESET: J2.6, TP_RESET.TP, U1.P$AC13 (P0.18/RESET)
SCK: U1.P$A12 (P0.02/AIN0); also elsewhere on the board
SCL: IC1.B1 (SCL), IC3.12 (SCX), R4.1, R17.2, TP_SCL.TP, U1.P$M2 (P0.07); also elsewhere on the board
SDA: IC1.C1 (SDA), IC3.2 (SDX), R2.1, R18.2, TP_SDA.TP, U1.P$L1 (P0.06); also elsewhere on the board
SWDCLK: J2.4, TP_SWDCLK.TP, U1.P$AA24 (SWDCLK)
SWDIO: J2.2, TP_SWDIO.TP, U1.P$AC24 (SWDIO)
SWO: TP_SWO.TP, U1.P$AD22 (P1.00)
VBAT: C37.2, IC1.C2 (BAT); also elsewhere on the board
VBUS: C21.1, C38.2, IC1.A2 (IN), U1.P$AD2 (VBUS); also elsewhere on the board
VREG: C23.2, C24.2, C39.1, IC1.B2 (SYS), IC9.A1 (EN), IC9.A2 (VIN_1), IC9.A3 (VIN_2), TP_VREG.TP

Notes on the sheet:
SWD
LiPo Charger
N.C.
DEC3
DEC4_6
DEC1
P0.00/XL1
P0.01/XL2
DC/DC
IMU

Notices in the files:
parts and their libraries:
COPYRIGHT: Copyright (C) 2024 Ultra Librarian. All rights reserved.
COPYRIGHT: Copyright (C) 2025 Ultra Librarian. All rights reserved.
